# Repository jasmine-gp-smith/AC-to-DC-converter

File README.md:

# AC-to-DC-converter (2023)
## SIMULATION
The simulation was completed as part of a microelectronics lab.\
The circuit was then implemented on a breadboard\
An oscilloscope and waveform generator were used to test the function of the AC to DC Converter

## PCB
I created this AC-to-DC PCB as one of my first PCB projects.\
The purpose was to learn the basics of KiCAD and PCB design.
### Schematic

### BOM
| Id | Designator     | Footprint                                   | Quantity | Designation | Supplier and ref |
|----|----------------|---------------------------------------------|----------|-------------|------------------|
| 1  | C1             | PCAP_4x5.4-ELECT_NCA                        | 1        | 25u         |                  |
| 2  | D1, D2, D3, D4 | D_0603_1608Metric_Pad1.05x0.95mm_HandSolder | 4        | 1N4148      |                  |
| 3  | D5             | D_0603_1608Metric_Pad1.05x0.95mm_HandSolder | 1        | D_Zener     |                  |
| 4  | J1             | PinHeader_1x01_P1.00mm_Vertical             | 1        | AC+         |                  |
| 5  | J2             | PinHeader_1x01_P1.00mm_Vertical             | 1        | AC-         |                  |
| 6  | J3             | PinHeader_1x01_P1.00mm_Vertical             | 1        | DC+         |                  |
| 7  | J4             | PinHeader_1x01_P1.00mm_Vertical             | 1        | DC-         |                  |
| 8  | R1             | R_0603_1608Metric_Pad0.98x0.95mm_HandSolder | 1        | 300         |                  |
### Stackup
### Layout

### 3D Preview
Click the preview image to view the 3D PCB

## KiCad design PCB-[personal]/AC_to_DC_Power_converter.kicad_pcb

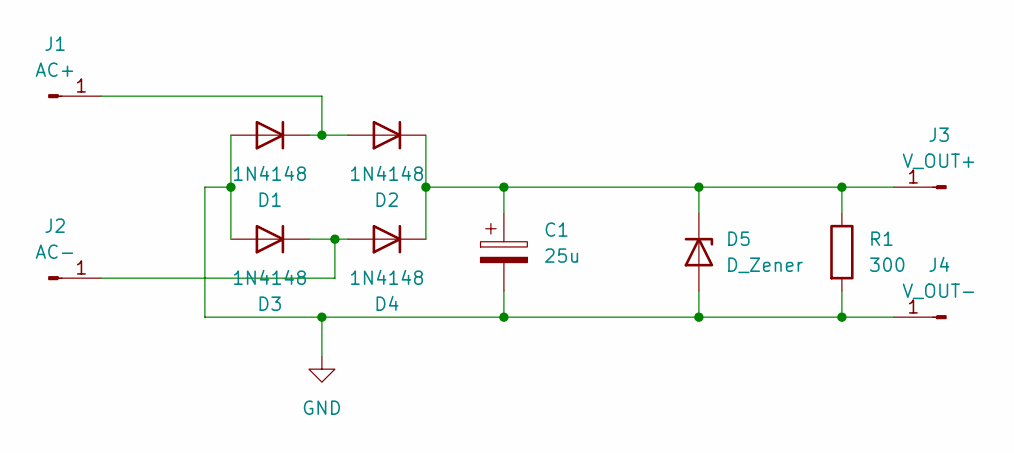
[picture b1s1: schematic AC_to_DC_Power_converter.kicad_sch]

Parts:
C1: 25u; CAP_WCAP-ASLI_04p0X05p5_WRE-M
D1, D2, D3, D4: 1N4148; SOD123_MCC-M
D5: D_Zener; SOD323_NEX-M
J1: AC+; PinHeader_1x01_P2.54mm_Vertical
J2: AC-; PinHeader_1x01_P2.54mm_Vertical
J3: V_OUT+; PinHeader_1x01_P2.54mm_Vertical
J4: V_OUT-; PinHeader_1x01_P2.54mm_Vertical
R1: 300; R_0603_1608Metric_Pad0.98x0.95mm_HandSolder

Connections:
GND: C1.2, D1.2 (A), D3.2 (A), D5.2 (A), J4.1, R1.2
unnamed: D1.1 (K), D2.2 (A), J1.1
unnamed: C1.1, D2.1 (K), D4.1 (K), D5.1 (K), J3.1, R1.1
unnamed: D3.1 (K), D4.2 (A), J2.1

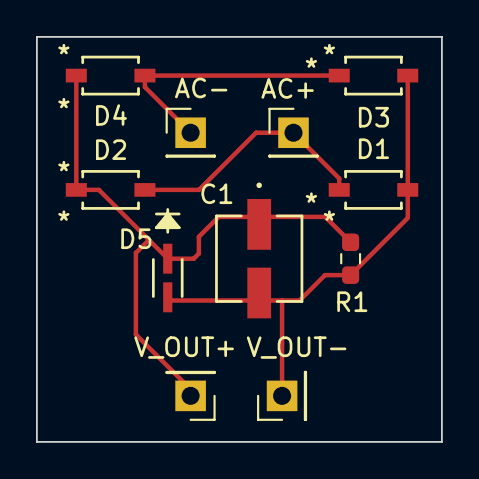
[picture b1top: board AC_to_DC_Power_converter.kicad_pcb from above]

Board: 2 copper layers, 22.5 x 22.5 mm, 11 parts (0 on the bottom side), 4 nets.

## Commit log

2023-10-26 Added KiCAD PCB and schematics files
2023-10-26 Added LtSpice files from project
2023-10-26 Fixing BOM
2026-04-20 Rename .stl to ACtoDC3d.stl
2026-04-20 Rename AC to DC Power converter.png to ACtoDCpreview.png
